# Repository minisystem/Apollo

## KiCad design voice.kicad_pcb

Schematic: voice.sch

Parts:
C1, C2: 0.01μ; SM0603-C-JRL
C3, C40, C41, C42, C43, C44, C45, C46, C47, C48, C49, C50, C51, C52, C53, C54, C55, C56, C57, C58, C59, C60, C61, C62, C63, C64, C65, C66, C67: 0.1μ; SM0603-C-JRL
C4: 10p; SM0603-C-JRL
C5, C12, C13: 0.47μ; jrl_c_elec_4x5.3
C6: 680p; SM0603-C-JRL
C7, C8, C9, C10: 270pF; SM0603-C-JRL
C11: 15p; SM0603-C-JRL
C14: 47pF; SM0603-C-JRL
D1, D2, D3, D4: 1N4148; SOD323-C1A2
J1: DDR3-DIMM; DDR3-DIMM-MO-269-mask-fix
Q1, Q2, Q3, Q4, Q10, Q11, Q14, Q15, Q17, Q18, Q20, Q39: 2SA1832; SOT416-SC75
Q5, Q6, Q7, Q8, Q9, Q12, Q13: 2SK208-GR; SOT23-132-JRL
Q16: 2SA1618; SOT-353_SC-70-5
Q19: 2SK208-GR; SC-59
Q21: 2SC4738; SOT416-SC75
R1, R4, R6, R74: 4.7meg; SM0603-R-JRL; Digikey P10.0KCCT-ND
R2: 47K; SM0603-R-JRL; Digikey P10.0KCCT-ND
R3, R5, R19, R49, R73, R76, R88, R89, R107, R252: 12K; SM0603-R-JRL; Digikey P10.0KCCT-ND
R7: 10K; SM0603-R-JRL; Digikey P10.0KCCT-ND
R8, R21: 12K; SM0603-R-JRL; Digikey P56.0KCCT-ND
R9, R105: 27K; SM0603-R-JRL; Digikey P56.0KCCT-ND
R10: 10K; SM0603-R-JRL; Digikey P56.0KCCT-ND
R11, R12, R13, R14: 330; SM0603-R-JRL; Digikey P10.0KCCT-ND
R15, R26, R43, R72, R91, R92, R95, R98, R103: 100K; SM0603-R-JRL; Digikey P10.0KCCT-ND
R16, R17, R28: 68K; SM0603-R-JRL; Digikey P56.0KCCT-ND
R18, R52: 33K; SM0603-R-JRL; Digikey P10.0KCCT-ND
R20: 15k; SM0603-R-JRL; Digikey P10.0KCCT-ND
R22, R30: 18K; SM0603-R-JRL; Digikey P10.0KCCT-ND
R23, R24: 510; SM0603-R-JRL; Digikey P10.0KCCT-ND
R25: 30K; SM0603-R-JRL; Digikey P10.0KCCT-ND
R27: 15K; SM0603-R-JRL; Digikey P10.0KCCT-ND
R29, R32, R114: 22K; SM0603-R-JRL; Digikey P56.0KCCT-ND
R31, R118: 22K; SM0603-R-JRL; Digikey P10.0KCCT-ND
R33, R48: 100K; SM0603-R-JRL
R34, R44: 150K; SM0603-R-JRL
R35: 10K; SM0603-R-JRL
R36, R109: 150K; SM0603-R-JRL; Digikey P10.0KCCT-ND
R37, R38, R39, R40: 18K; SM0603-R-JRL
R41: 22K; SM0603-R-JRL
R42, R53, R104: 1.5K; SM0603-R-JRL
R45, R46, R47, R65, R66, R67, R68: 68K; SM0603-R-JRL
R50, R51, R63, R64, R80, R81, R82, R83, R96, R97, R100, R101, R111, R112, R254, R255: 470; SM0603-R-JRL; Digikey P10.0KCCT-ND
R54, R55, R56, R57: 33K; SM0603-R-JRL
R58, R75, R79, R84, R253: 47K; SM0603-R-JRL; Digikey P56.0KCCT-ND
R59, R60, R61, R62: 560; SM0603-R-JRL
R69, R113: 1meg; SM0603-R-JRL; Digikey P10.0KCCT-ND
R70, R71, R86, R256: 18K; SM0603-R-JRL; Digikey P56.0KCCT-ND
R77: 2.2K; SM0603-R-JRL; Digikey P10.0KCCT-ND
R78, R85: 1meg; SM0603-R-JRL
R87: 470K; SM0603-R-JRL; Digikey P10.0KCCT-ND
R90, R94, R115, R117: 68K; SM0603-R-JRL; Digikey P10.0KCCT-ND
R93: 27K; SM0603-R-JRL; Digikey P10.0KCCT-ND
R99: 1K 3300 ppm/K; SM0805-HAND
R102: 56K; SM0603-R-JRL; Digikey P56.0KCCT-ND
R106: 1.5M; SM0603-R-JRL
R108: 43K; SM0603-R-JRL; Digikey P56.0KCCT-ND
R110: 180K; SM0603-R-JRL; Digikey P10.0KCCT-ND
R116: 82K; SM0603-R-JRL; Digikey P10.0KCCT-ND
TP1, TP2, TP3, TP4, TP5, TP6, TP7, TP8, TP9: TEST_POINT; TEST_POINT_SMALL
U1, U4: CD4053; TSSOP-16_4.4x5mm_Pitch0.65mm_jrl
U2, U5, U7, U8, U9, U10, U12, U14: LM13700; SO16-JRL
U3, U6, U13, U16: TA75S558F; SOT753_TSOP5_SC-74A
U11: TL072-; TSSOP8-JRL
U15: RC4558; TSSOP8-JRL

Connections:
+10V: R25.2; also elsewhere on the board
+12V: C40.1, C41.1, C42.1, C43.1, C44.1, C45.1, C46.1, C47.1, C48.1, C49.1, C50.1, C51.1, C52.1, C53.1, J1.2, J1.18, J1.36, J1.51, J1.61, J1.76, J1.87, J1.103, Q5.2 (S), Q6.2 (S), Q7.2 (S), Q8.2 (S), Q9.2 (S), R3.2, R5.2, R19.2, R31.2, R49.2, R69.2, R73.2, R76.2, R88.2, R89.2, R107.2, R252.2, U1.16 (Vdd), U2.11 (V+), U3.5 (V+), U4.16 (Vdd), U5.11 (V+), U6.5 (V+), U7.11 (V+), U8.11 (V+), U9.11 (V+), U10.11 (V+), U11.8 (V+), U12.11 (V+), U13.5 (V+), U14.11 (V+), U15.8 (V+), U16.5 (V+); also elsewhere on the board
-5V: U1.7 (Vee), U4.7 (Vee); also elsewhere on the board
-12V: C54.2, C55.2, C56.2, C57.2, C58.2, C59.2, C60.2, C61.2, C62.2, C63.2, C64.2, C65.2, C66.2, C67.2, J1.4, J1.20, J1.38, J1.53, J1.63, J1.78, J1.89, J1.105, R52.1, R54.1, R55.1, R56.1, R57.1, R106.2, U2.6 (V-), U3.2 (V-), U5.6 (V-), U6.2 (V-), U7.6 (V-), U8.6 (V-), U9.6 (V-), U10.6 (V-), U11.4 (V-), U12.6 (V-), U13.2 (V-), U14.6 (V-), U15.4 (V-), U16.2 (V-); also elsewhere on the board
AUX: J1.108, R253.1
AUX_LEVEL: J1.107, R256.1
CROSSMOD: J1.29, R16.1
ENV1_A: J1.94; also elsewhere on the board
ENV1_D: J1.95; also elsewhere on the board
ENV1_POL: J1.91; also elsewhere on the board
ENV1_R: J1.97; also elsewhere on the board
ENV1_S: J1.96; also elsewhere on the board
ENV2_A: J1.98; also elsewhere on the board
ENV2_D: J1.99; also elsewhere on the board
ENV2_R: J1.101; also elsewhere on the board
ENV2_S: J1.100; also elsewhere on the board
ENV_1: Q19.1 (D), R9.1, R20.2, R113.2; also elsewhere on the board
ENV_2: R102.2, R116.2; also elsewhere on the board
ENV_SEL: D3.1 (K), J1.72, R117.1
GATE: J1.92; also elsewhere on the board
HPF: J1.59, R71.1
Iabc: Q16.5 (C), R37.2, R38.2, R39.2, R40.2
KCV_1: J1.6, R95.1; also elsewhere on the board
KCV_2: J1.40; also elsewhere on the board
LEVEL: J1.83, R98.1
LFO: J1.55, R27.1
NOISE: J1.22; also elsewhere on the board
unnamed: C1.1, R1.1, R2.1, R15.2, U2.5, U3.3 (-)
unnamed: C1.2, R2.2, R7.1, R10.1, TP1.1, U3.4
unnamed: C2.1, R18.1, R26.2, U6.3 (-), U10.5
unnamed: C3.1, R34.1
unnamed: C3.2, Q5.1 (D), R36.2, R44.1, R52.2, TP2.1
unnamed: C4.1, C6.2, R43.2, TP3.1, U11.1
unnamed: C4.2, R43.1, U5.5, U5.12, U10.12, U11.2 (-)
unnamed: C5.1 (+), R48.2
unnamed: C5.2 (-), Q9.1 (D), Q12.1 (D), R57.2, R68.1, R78.2, TP5.1
unnamed: C6.1, Q5.3 (G), U7.5
unnamed: C7.1, Q6.3 (G), U8.5
unnamed: C8.1, Q7.3 (G), U8.12
unnamed: C9.1, Q8.3 (G), U9.5
unnamed: C10.1, Q9.3 (G), U9.12
unnamed: C11.1, R72.1, U12.5, U13.3 (-)
unnamed: C11.2, R72.2, R77.1, TP6.1, U13.4
unnamed: C12.1 (+), Q12.2 (S)
unnamed: C12.2 (-), R75.1
unnamed: C13.1 (+), Q13.2 (S)
unnamed: C13.2 (-), R84.1
unnamed: C14.1, R104.2, U16.4
unnamed: C14.2, Q16.4 (C), R106.1, U16.3 (-)
unnamed: D1.2 (A), Q12.3 (G), R78.1
unnamed: D2.2 (A), Q13.3 (G), R85.1
unnamed: D3.2 (A), Q19.3 (G), R113.1
unnamed: D4.1 (K), R117.2, R118.1
unnamed: Q1.2 (E), R16.2
unnamed: Q1.3 (C), U2.16
unnamed: Q2.2 (E), R17.2
unnamed: Q2.3 (C), U2.1
unnamed: Q3.2 (E), R28.2
unnamed: Q3.3 (C), U10.1
unnamed: Q4.2 (E), R41.2
unnamed: Q4.3 (C), U7.16
unnamed: Q6.1 (D), R45.2, R54.2, R65.1
unnamed: Q8.1 (D), R47.2, R56.2, R67.1
unnamed: Q10.2 (E), R70.2
unnamed: Q10.3 (C), U5.16
unnamed: Q11.2 (E), R69.1, R71.2
unnamed: Q11.3 (C), U7.1
unnamed: Q7.1 (D), Q13.1 (D), R46.2, R55.2, R66.1, R85.2, TP4.1
unnamed: Q14.2 (E), U12.12
unnamed: Q14.3 (C), U12.1
unnamed: Q15.2 (E), R86.2
unnamed: Q15.3 (C), U5.1
unnamed: Q16.1 (B), R93.2, R99.1, TP8.1
unnamed: Q16.2 (E), R104.1
unnamed: Q17.2 (E), R102.1
unnamed: Q17.3 (C), U12.16
unnamed: Q18.2 (E), R105.1
unnamed: Q18.3 (C), U14.16
unnamed: Q19.2 (S), R109.2
unnamed: Q20.2 (E), R114.1
unnamed: Q20.3 (C), U14.1
unnamed: Q21.1 (B), R118.2
unnamed: Q21.3 (C), R115.2, R116.1
unnamed: Q39.2 (E), R256.2
unnamed: Q39.3 (C), U10.16
unnamed: R3.1, U2.15
unnamed: R5.1, U2.2
unnamed: R7.2, U1.2 (Y0)
unnamed: R10.2, U1.12 (Y0)
unnamed: R8.2, R11.2, U2.14 (+)
unnamed: R4.1, R12.2, U2.13 (-)
unnamed: R9.2, R13.2, U2.3 (+)
unnamed: R6.1, R14.2, U2.4 (-)
unnamed: R19.1, U10.2
unnamed: R20.1, R22.2, U4.5 (Y0)
unnamed: R21.1, U4.15 (Z)
unnamed: R21.2, R23.2, U10.3 (+)
unnamed: R24.2, U10.4 (-)
unnamed: R25.1, R27.2, U4.3 (Y1)
unnamed: R29.2, U4.9 (S)
unnamed: R30.2, R31.1, U4.2 (Y0)
unnamed: R32.2, U4.10 (S)
unnamed: R33.1, R42.1, U7.14 (+)
unnamed: R33.2, R34.2, R35.2
unnamed: R36.1, R50.2, U7.4 (-)
unnamed: R37.1, U8.1
unnamed: R38.1, U8.16
unnamed: R39.1, U9.1
unnamed: R40.1, U9.16
unnamed: R44.2, R59.2, R65.2, U7.12, U8.4 (-)
unnamed: R45.1, R60.2, R66.2, U8.13 (-)
unnamed: R46.1, R61.2, R67.2, U9.4 (-)
unnamed: R47.1, R62.2, R68.2, U9.13 (-)
unnamed: R48.1, R53.2, U7.13 (-)
unnamed: R49.1, U5.15
unnamed: R51.2, U7.3 (+)
unnamed: R58.2, R63.2, U5.13 (-)
unnamed: R64.2, U5.14 (+)
unnamed: R73.1, U12.2
unnamed: R74.1, R81.2, U12.3 (+)
unnamed: R75.2, R80.2, R84.2, TP7.1, U12.4 (-)
unnamed: R76.1, U5.2
unnamed: R79.2, R82.2, U5.4 (-)
unnamed: R83.2, U5.3 (+)
unnamed: R88.1, U12.15
unnamed: R89.1, U14.15
unnamed: R90.2, R93.1, U15.7
unnamed: R91.1, R92.2, U15.2 (-)
unnamed: R91.2, R94.1, U15.1
unnamed: R96.2, U12.13 (-)
unnamed: R97.2, R98.2, U12.14 (+)
unnamed: R100.2, U14.13 (-)
unnamed: R94.2, R101.2, U14.14 (+)
unnamed: R95.2, R103.2, U15.3 (+)
unnamed: R107.1, U14.2
unnamed: R87.1, R90.1, R108.1, R110.2, U14.5, U14.12, U15.6 (-)
unnamed: R109.1, R111.2, R115.1, TP9.1, U14.3 (+)
unnamed: R112.2, U14.4 (-)
unnamed: R252.1, U10.15
unnamed: R253.2, R254.2, U10.13 (-)
unnamed: R255.2, U10.14 (+)
unnamed: U4.1 (Y1), U4.4 (Z)
unnamed: U11.6 (-), U11.7
OUT: J1.85, R77.2
PW/PWM: J1.26, R32.1
PWM: C2.2, R18.2, U6.4; also elsewhere on the board
PWM_LEVEL: J1.28, R28.1
PWM_SEL: J1.25, R29.1
RES_CTRL: J1.80, R41.1
SYNC_CTRL: J1.14; also elsewhere on the board
VCA_BAL: J1.82, R74.2
VCF_12dB: D2.1 (K), J1.73
VCF_24dB: D1.1 (K), J1.74
VCF_CUTOFF: J1.69, R108.2
VCF_ENV_MOD: J1.70, R114.2
VCF_KF: J1.67, R105.2
VCF_TUNE: J1.68, R87.2
VCO1: R58.1; also elsewhere on the board
VCO1_AUTOTUNE: J1.12; also elsewhere on the board
VCO1_INIT: J1.8; also elsewhere on the board
VCO1_LEVEL: J1.57, R70.1
VCO1_MOD: U1.15 (Z); also elsewhere on the board
VCO1_MOD_SUM: J1.9; also elsewhere on the board
VCO1_MOD_SW: J1.23, U1.10 (S)
VCO1_RANGE: J1.65, R92.1
VCO1_TRI_SYM: J1.10; also elsewhere on the board
VCO1_WF-0: J1.15; also elsewhere on the board
VCO1_WF-1: J1.16; also elsewhere on the board
VCO1_XMOD: U2.12; also elsewhere on the board
VCO2: R8.1, R79.1; also elsewhere on the board
VCO2_AUTOTUNE: J1.46; also elsewhere on the board
VCO2_INIT: J1.42; also elsewhere on the board
VCO2_LEVEL: J1.58, R86.1
VCO2_MOD: U1.14 (Z); also elsewhere on the board
VCO2_MOD_SUM: J1.43; also elsewhere on the board
VCO2_MOD_SW: J1.24, U1.11 (S)
VCO2_TRI_SYM: J1.44; also elsewhere on the board
VCO2_WF-0: J1.48; also elsewhere on the board
VCO2_WF-1: J1.49; also elsewhere on the board
VCO_ENV_MOD: J1.31, R17.1
VCO_ENV_MOD_BAL: J1.32, R6.2
VCO_LFO_MOD: J1.33, R15.1
VCO_MOD_BAL: J1.34, R1.2
XMOD_BAL: J1.30, R4.2

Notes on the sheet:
VCF Exponential converter
check polarity
SIMULATE VCA CONTROL
56K - 100K
18K-28K
SIMULATE VCF CONTROL need to change to low offset low Iabc configuration
22K - 32K
39K - 49K
VCF CONTROL
low offset LM13700: increase input level, reduce Iabc relative to BA662 configuration
(180K)
+10V reference in JP8
VCF CUTOFF is the sum of CUTOFF, LFO, VCF PEDAL and VCF MOD
(100K)
LFO modulation generated from one VCA on each module controller board (2 MCBs for 2 part timbrality)
VOICE MODULE
CROSS MODULATION
VCO PITCH MODULATION
VCF MODULATION
PULSE WIDTH MODULATION
VCA
HPF
VC MIXER
VCF
24 dB/oct
12 dB/oct
'LEVEL' is stepped LFO modulation offset and controlled by 'VCA LEVEL' CV - see MCB
CD4053s are separate ICs on JP8 module board. Because of cross talk?
Maybe JFET shunts here?
Simulated. Need to investigate further and test original JP8 VCA modulation behaviour. Not getting good offness when LEVEL CV is 0V.
J112 Vgs(off) isn't low enough to block -ve inverted envelope voltages with -11V gate. Lower ENV amplitude or find different FET? ON Semi TF412S has low Vgs{off) - will probably work 2SK932 and J201 also look promising
ENV_SEL needs to swing close +ve and -ve rail. To keep JFET off need <= -11V.
When LEVEL CV = 0V there is some bleedthrough of ENV_2 signal. When LEVEL CV < 0V then there is no output. Amount of bleedthrough varies from voice to voice of JP8
OFFSET
-11V to +12V
-11V to +12V switch
10V switch
MOD CONTROL CV
DIRECT CV
OUTPUT

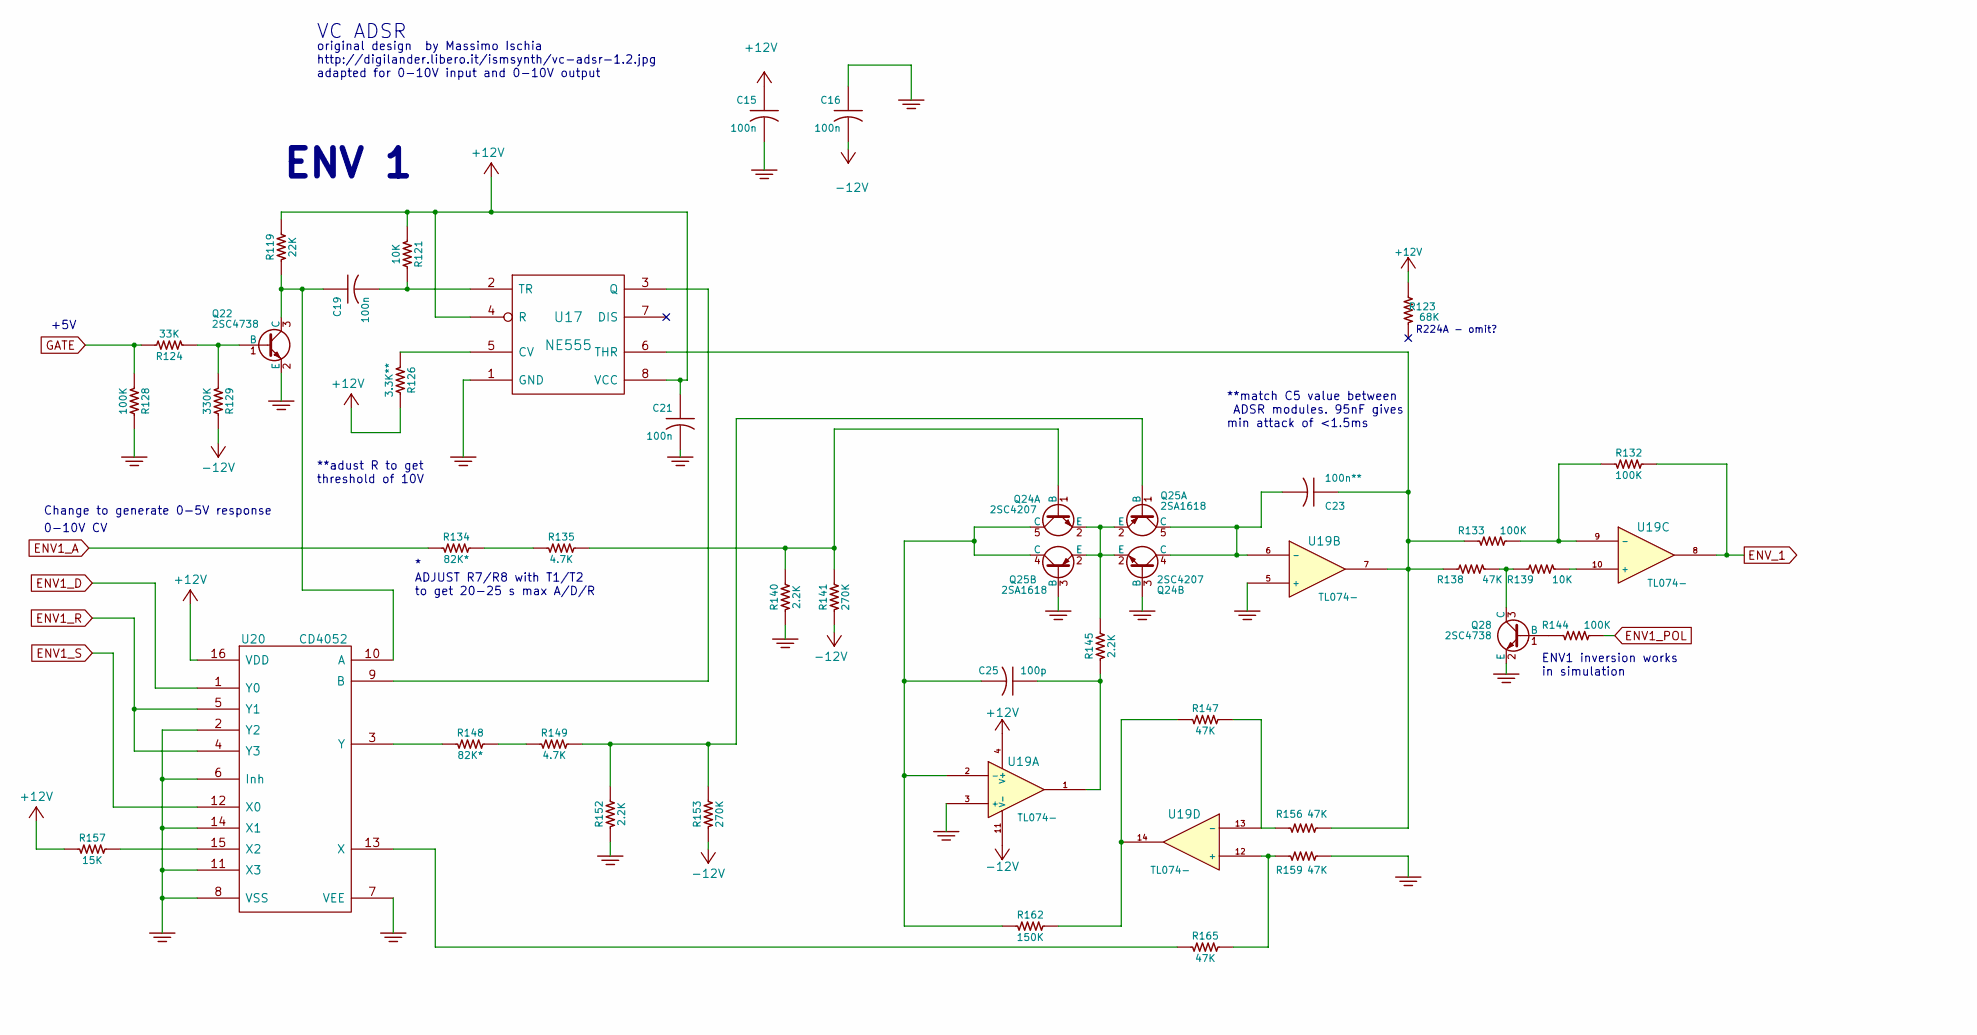
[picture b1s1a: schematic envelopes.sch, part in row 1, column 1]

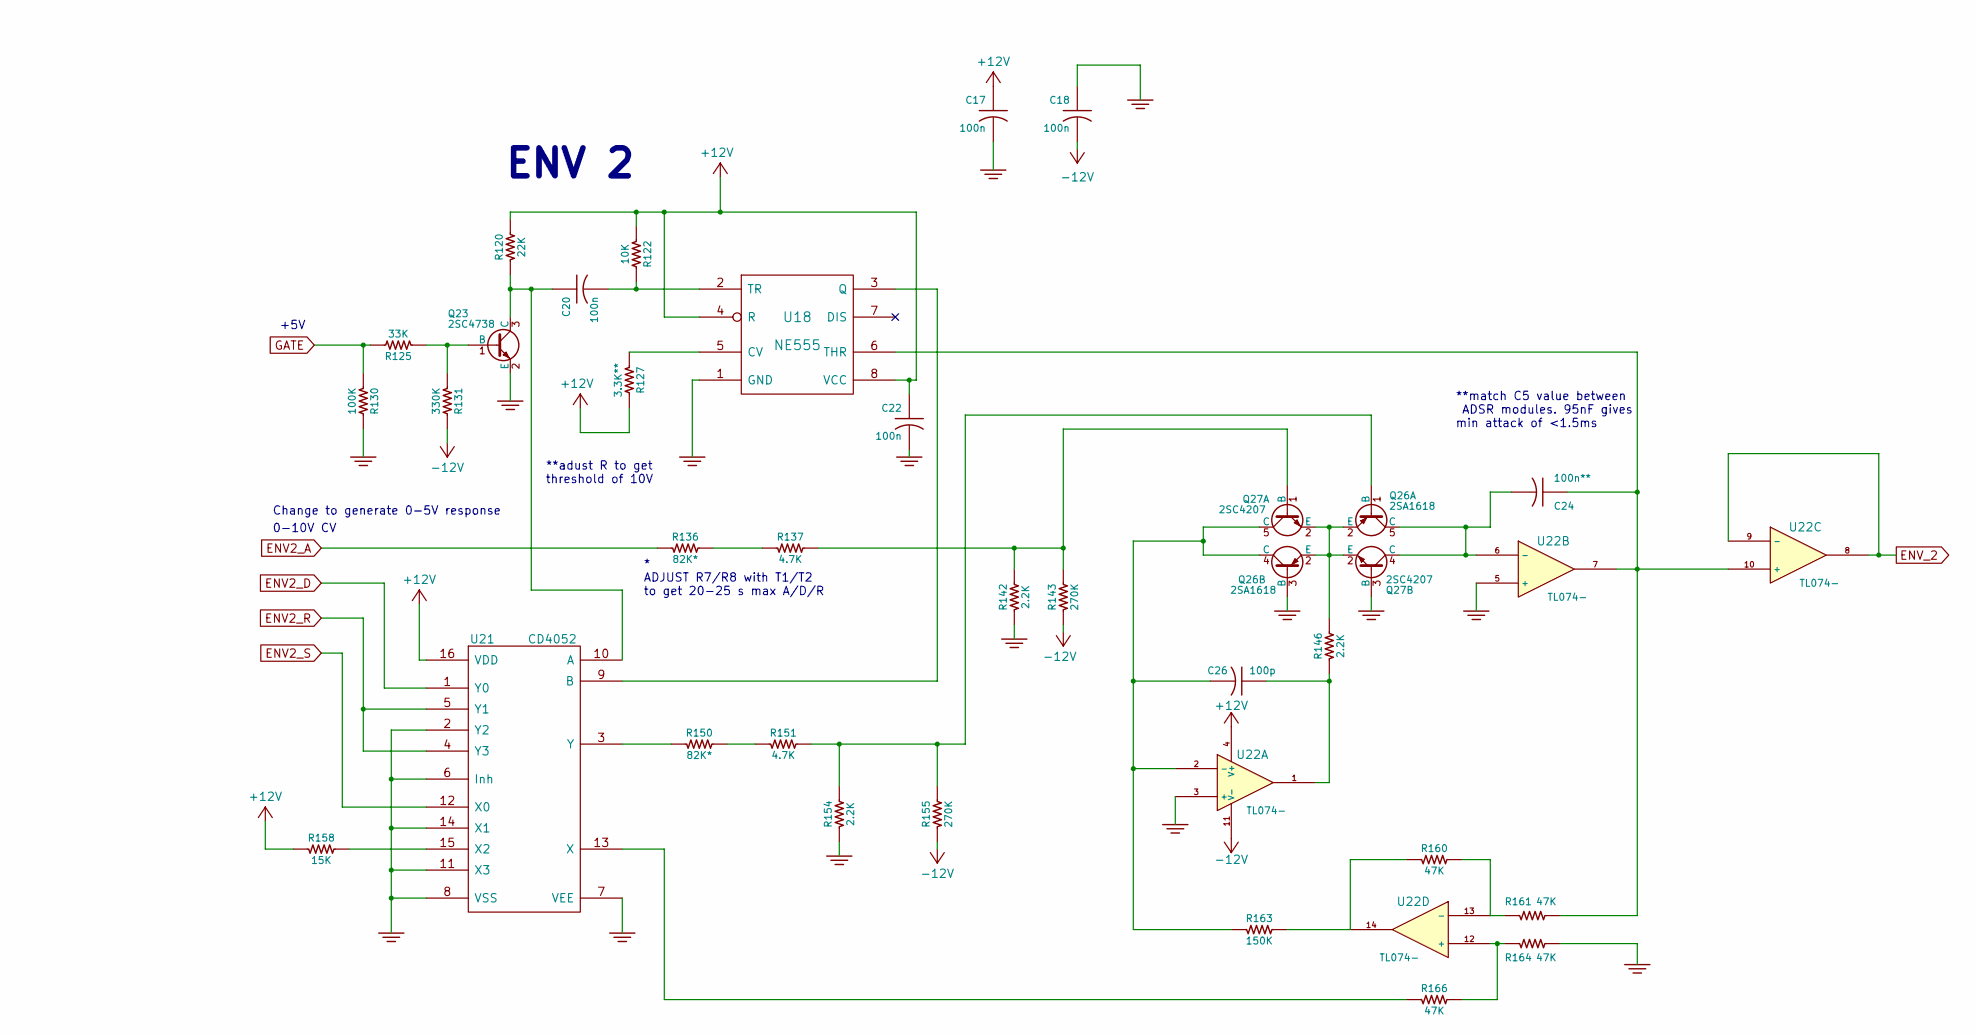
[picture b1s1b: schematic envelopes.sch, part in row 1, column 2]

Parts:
C15, C16, C17, C18, C19, C20, C21, C22: 100n; SM0603-C-JRL
C23, C24: 100n**; SM0603-C-JRL
C25, C26: 100p; SM0603-C-JRL
Q22, Q23, Q28: 2SC4738; SOT416-SC75
Q24, Q27: 2SC4207; SOT-353_SC-70-5
Q25, Q26: 2SA1618; SOT-353_SC-70-5
R119, R120: 22K; SM0603-R-JRL
R121, R122, R139: 10K; SM0603-R-JRL
R123: 68K; SM0603-R-JRL; Digikey P10.0KCCT-ND
R124, R125: 33K; SM0603-R-JRL
R126, R127: 3.3K**; SM0603-R-JRL
R128, R130, R132, R133, R144: 100K; SM0603-R-JRL
R129, R131: 330K; SM0603-R-JRL
R134, R136, R148, R150: 82K*; SM0603-R-JRL
R135, R137, R149, R151: 4.7K; SM0603-R-JRL
R138, R147, R156, R159, R160, R161, R164, R165, R166: 47K; SM0603-R-JRL
R140, R142, R145, R146, R152, R154: 2.2K; SM0603-R-JRL
R141, R143, R153, R155: 270K; SM0603-R-JRL
R157, R158: 15K; SM0603-R-JRL
R162, R163: 150K; SM0603-R-JRL
U17, U18: NE555; TSSOP8-JRL
U19, U22: TL074-; TSSOP-14_4.4x5mm_Pitch0.65mm
U20, U21: CD4052; TSSOP-16_4.4x5mm_Pitch0.65mm

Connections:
+12V: C15.1, C17.1, C21.1, C22.1, R119.2, R120.2, R121.1, R122.1, R123.2, R126.2, R127.2, R157.1, R158.1, U17.4 (R), U17.8 (VCC), U18.4 (R), U18.8 (VCC), U19.4 (V+), U20.16 (VDD), U21.16 (VDD), U22.4 (V+); also elsewhere on the board
-12V: C16.2, C18.2, R129.2, R131.2, R141.1, R143.1, R153.1, R155.1, U19.11 (V-), U22.11 (V-); also elsewhere on the board
ENV1_A: R134.1; also elsewhere on the board
ENV1_D: U20.1 (Y0); also elsewhere on the board
ENV1_POL: R144.2; also elsewhere on the board
ENV1_R: U20.4 (Y3), U20.5 (Y1); also elsewhere on the board
ENV1_S: U20.12 (X0); also elsewhere on the board
ENV2_A: R136.1; also elsewhere on the board
ENV2_D: U21.1 (Y0); also elsewhere on the board
ENV2_R: U21.4 (Y3), U21.5 (Y1); also elsewhere on the board
ENV2_S: U21.12 (X0); also elsewhere on the board
ENV_1: R132.2, U19.8; also elsewhere on the board
ENV_2: U22.8, U22.9 (-); also elsewhere on the board
GATE: R124.2, R125.2, R128.1, R130.1; also elsewhere on the board
unnamed: C19.1, Q22.3 (C), R119.1, U20.10 (A)
unnamed: C19.2, R121.2, U17.2 (TR)
unnamed: C20.1, Q23.3 (C), R120.1, U21.10 (A)
unnamed: C20.2, R122.2, U18.2 (TR)
unnamed: C23.1, R133.1, R138.1, R156.2, U17.6 (THR), U19.7
unnamed: C23.2, Q24.4 (C), Q25.5 (C), U19.6 (-)
unnamed: C24.1, R161.2, U18.6 (THR), U22.7, U22.10 (+)
unnamed: C24.2, Q26.5 (C), Q27.4 (C), U22.6 (-)
unnamed: C25.1, R145.1, U19.1
unnamed: C25.2, Q24.5 (C), Q25.4 (C), R162.1, U19.2 (-)
unnamed: C26.1, R146.1, U22.1
unnamed: C26.2, Q26.4 (C), Q27.5 (C), R163.1, U22.2 (-)
unnamed: Q22.1 (B), R124.1, R129.1
unnamed: Q23.1 (B), R125.1, R131.1
unnamed: Q24.1 (B), R135.2, R140.2, R141.2
unnamed: Q24.2 (E), Q25.2 (E), R145.2
unnamed: Q25.1 (B), R149.2, R152.2, R153.2
unnamed: Q26.1 (B), R151.2, R154.2, R155.2
unnamed: Q26.2 (E), Q27.2 (E), R146.2
unnamed: Q27.1 (B), R137.2, R142.2, R143.2
unnamed: Q28.1 (B), R144.1
unnamed: Q28.3 (C), R138.2, R139.1
unnamed: R126.1, U17.5 (CV)
unnamed: R127.1, U18.5 (CV)
unnamed: R132.1, R133.2, U19.9 (-)
unnamed: R134.2, R135.1
unnamed: R136.2, R137.1
unnamed: R139.2, U19.10 (+)
unnamed: R147.1, R162.2, U19.14
unnamed: R147.2, R156.1, U19.13 (-)
unnamed: R148.1, U20.3 (Y)
unnamed: R148.2, R149.1
unnamed: R150.1, U21.3 (Y)
unnamed: R150.2, R151.1
unnamed: R157.2, U20.15 (X2)
unnamed: R158.2, U21.15 (X2)
unnamed: R159.1, R165.2, U19.12 (+)
unnamed: R160.1, R163.2, U22.14
unnamed: R160.2, R161.1, U22.13 (-)
unnamed: R164.1, R166.2, U22.12 (+)
unnamed: R165.1, U20.13 (X)
unnamed: R166.1, U21.13 (X)
unnamed: U17.3 (Q), U20.9 (B)
unnamed: U18.3 (Q), U21.9 (B)

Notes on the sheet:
**adust R to get threshold of 10V
* ADJUST R7/R8 with T1/T2 to get 20-25 s max A/D/R
**match C5 value between ADSR modules. 95nF gives min attack of <1.5ms
0-10V CV
+5V
VC ADSR
original design by Massimo Ischia http://digilander.libero.it/ismsynth/vc-adsr-1.2.jpg adapted for 0-10V input and 0-10V output
ENV1 inversion works in simulation
R224A - omit?
ENV 1
ENV 2
Change to generate 0-5V response

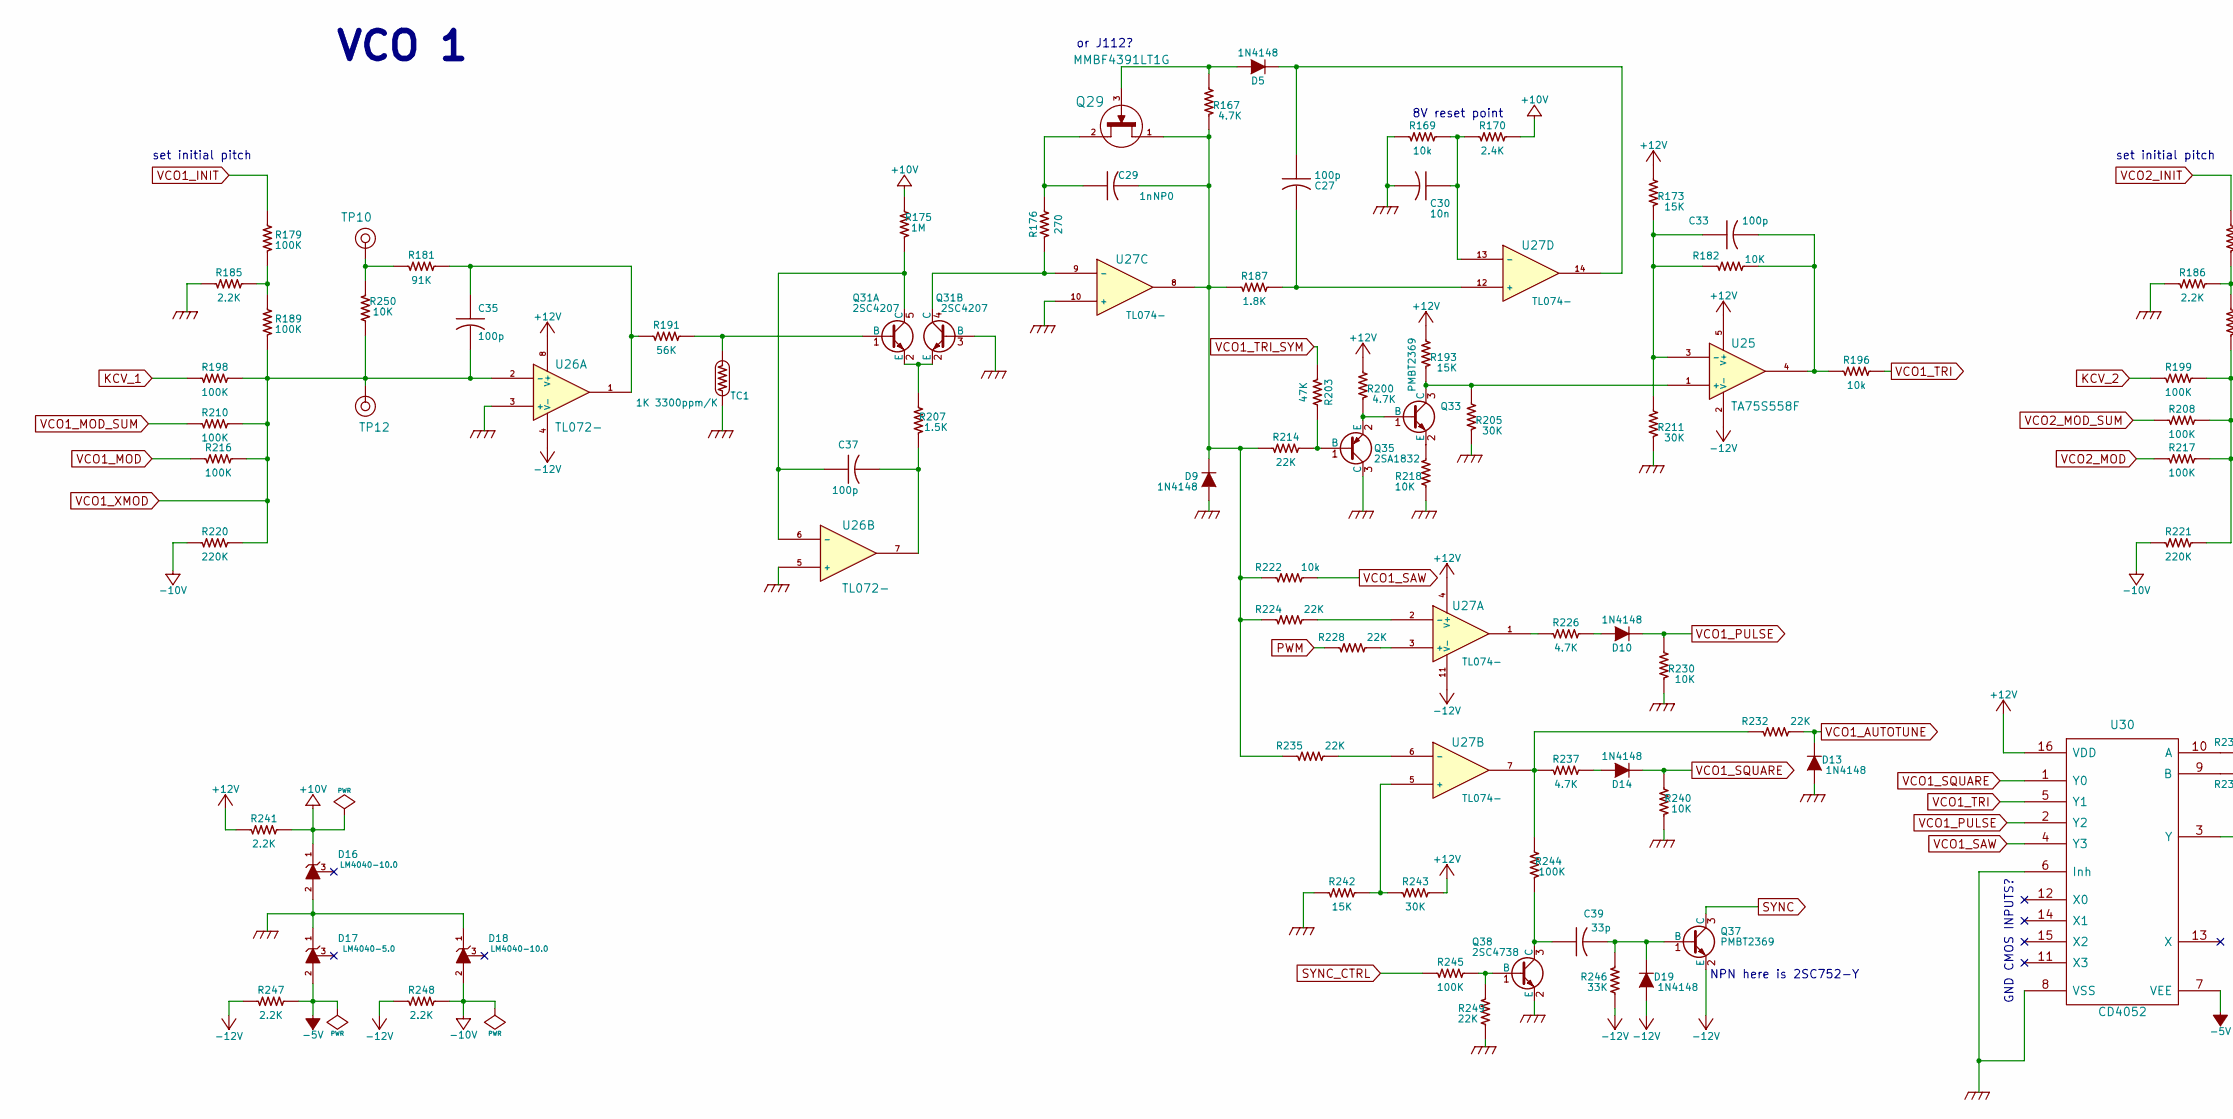
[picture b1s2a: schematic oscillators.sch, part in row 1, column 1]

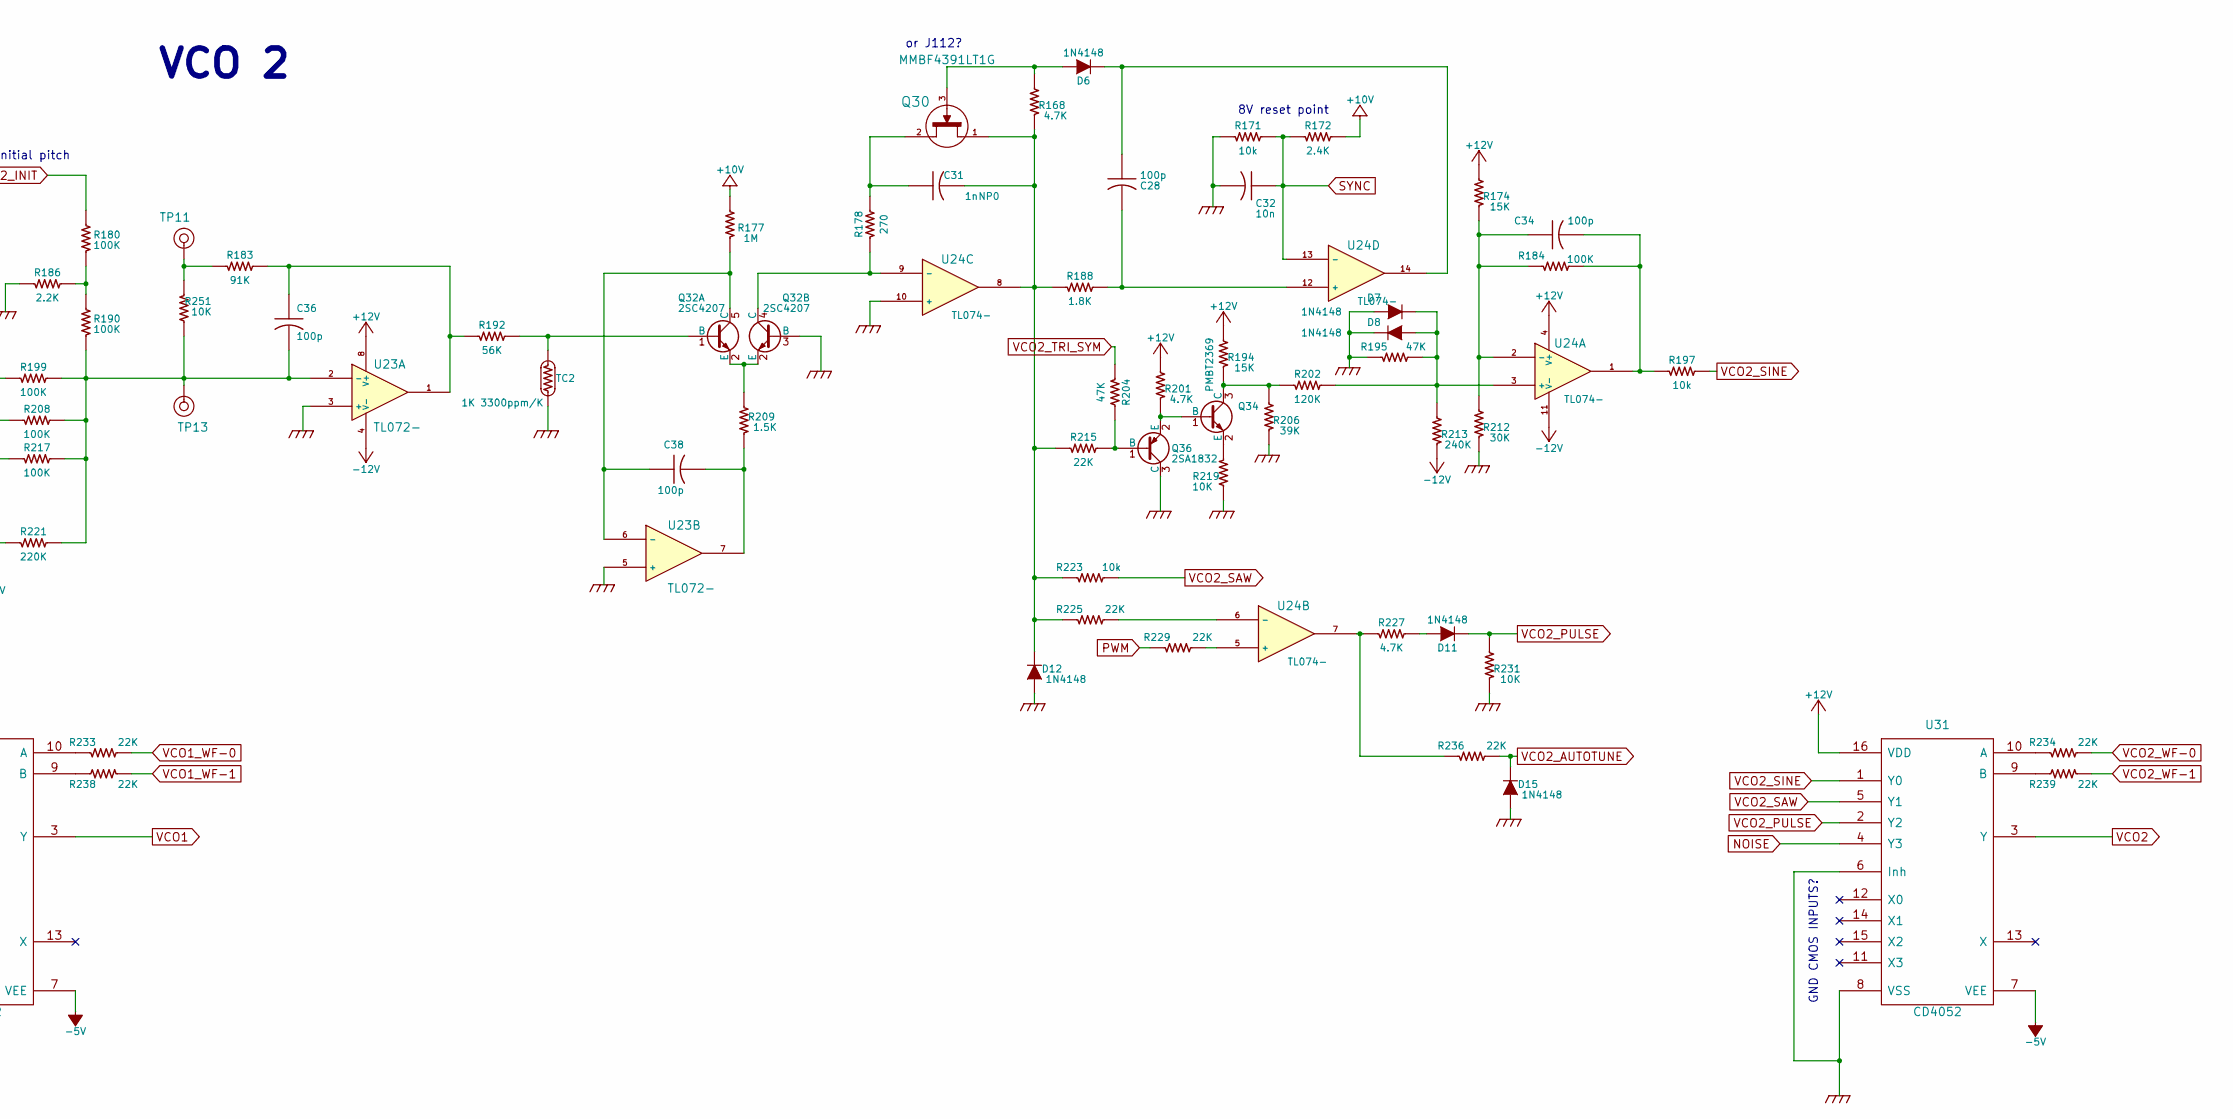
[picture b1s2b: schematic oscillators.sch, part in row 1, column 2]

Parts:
C27, C28, C33, C34: 100p; SM0603-C-JRL
C29, C31: 1n; SM0805-HAND-C
C30, C32: 10n; SM0603-C-JRL
C35, C36, C37, C38: 100p; SM0603-C-JRL; Digikey 399-1122-1-ND
C39: 33p; SM0603-C-JRL
D5, D6, D7, D8, D9, D10, D11, D12, D13, D14, D15, D19: 1N4148; SOD323-C1A2
D16, D18: LM4040-10.0; SOT23-132-JRL
D17: LM4040-5.0; SOT23-132-JRL
Q29, Q30: MMBF4391LT1G; SOT23-132-JRL
Q31, Q32: 2SC4207; SOT753_TSOP5_SC-74A
Q33, Q34, Q37: PMBT2369; SOT23-132-JRL
Q35, Q36: 2SA1832; SOT416-SC75
Q38: 2SC4738; SOT416-SC75
R167, R168, R200, R201, R226, R227, R237: 4.7K; SM0603-R-JRL; Digikey P10.0KCCT-ND
R169, R171, R196, R197, R222, R223: 10k; SM0603-R-JRL; Digikey P10.0KCCT-ND
R170, R172: 2.4K; SM0603-R-JRL; Digikey P10.0KCCT-ND
R173, R174, R193, R194, R242: 15K; SM0603-R-JRL; Digikey P10.0KCCT-ND
R175, R177: 1M; SM0603-R-JRL; Digikey P1.50MCCT-ND
R176, R178: 270; SM0603-R-JRL; Digikey P10.0KCCT-ND
R179, R180, R184, R189, R190, R244, R245: 100K; SM0603-R-JRL; Digikey P10.0KCCT-ND
R181, R183: 91K; SM0603-R-JRL; Digikey P91.0KCCT-ND
R182, R218, R219, R230, R231, R240: 10K; SM0603-R-JRL; Digikey P10.0KCCT-ND
R185, R186: 2.2K; SM0603-R-JRL; Digikey P91.0KCCT-ND
R187, R188: 1.8K; SM0603-R-JRL; Digikey P10.0KCCT-ND
R191, R192: 56K; SM0603-R-JRL; Digikey P56.0KCCT-ND
R195, R203, R204: 47K; SM0603-R-JRL; Digikey P10.0KCCT-ND
R198, R199, R208, R210, R216, R217: 100K; SM0603-R-JRL; Digikey P91.0KCCT-ND
R202: 120K; SM0603-R-JRL; Digikey P10.0KCCT-ND
R205, R211, R212, R243: 30K; SM0603-R-JRL; Digikey P10.0KCCT-ND
R206: 39K; SM0603-R-JRL; Digikey P10.0KCCT-ND
R207, R209: 1.5K; SM0603-R-JRL; Digikey P10.0KCCT-ND
R213: 240K; SM0603-R-JRL; Digikey P10.0KCCT-ND
R214, R215, R224, R225, R228, R229, R232, R233, R234, R235, R236, R238, R239, R249: 22K; SM0603-R-JRL; Digikey P10.0KCCT-ND
R220, R221: 220K; SM0603-R-JRL; Digikey P91.0KCCT-ND
R241, R247, R248: 2.2K; SM0603-R-JRL; Digikey P10.0KCCT-ND
R246: 33K; SM0603-R-JRL; Digikey P10.0KCCT-ND
R250, R251: 10K; SM0603-R-JRL; Digikey P56.0KCCT-ND
TC1, TC2: 1K 3300ppm/K; SM0805-HAND
TP10, TP11, TP12, TP13: TEST_POINT; TEST_POINT_SMALL
U23, U26: TL072-; TSSOP8-JRL
U24, U27: TL074-; TSSOP-14_4.4x5mm_Pitch0.65mm
U25: TA75S558F; SOT753_TSOP5_SC-74A
U30, U31: CD4052; TSSOP-16_4.4x5mm_Pitch0.65mm_jrl

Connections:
+10V: D16.1 (K), R170.2, R172.2, R175.2, R177.2, R241.2; also elsewhere on the board
+12V: R173.2, R174.2, R193.2, R194.2, R200.2, R201.2, R241.1, R243.2, U23.8 (V+), U24.4 (V+), U25.5 (V+), U26.8 (V+), U27.4 (V+), U30.16 (VDD), U31.16 (VDD); also elsewhere on the board
-5V: D17.2 (A), R247.2, U30.7 (VEE), U31.7 (VEE); also elsewhere on the board
-10V: D18.2 (A), R220.1, R221.1, R248.2
-12V: D19.2 (A), Q37.2 (E), R213.1, R246.1, R247.1, R248.1, U23.4 (V-), U24.11 (V-), U25.2 (V-), U26.4 (V-), U27.11 (V-); also elsewhere on the board
KCV_1: R198.1; also elsewhere on the board
KCV_2: R199.1; also elsewhere on the board
NOISE: U31.4 (Y3); also elsewhere on the board
unnamed: C27.1, D5.1 (K), U27.14
unnamed: C27.2, R187.2, U27.12 (+)
unnamed: C28.1, D6.1 (K), U24.14
unnamed: C28.2, R188.2, U24.12 (+)
unnamed: C29.1, Q29.2 (S), R176.2
unnamed: C29.2, D9.1 (K), Q29.1 (D), R167.1, R187.1, R214.1, R222.1, R224.1, R235.1, U27.8
unnamed: C30.1, R169.2, R170.1, U27.13 (-)
unnamed: C31.1, Q30.2 (S), R178.2
unnamed: C31.2, D12.1 (K), Q30.1 (D), R168.1, R188.1, R215.1, R223.1, R225.1, U24.8
unnamed: C33.1, R173.1, R182.1, R211.2, U25.3 (-)
unnamed: C33.2, R182.2, R196.1, U25.4
unnamed: C34.1, R174.1, R184.1, R212.2, U24.2 (-)
unnamed: C34.2, R184.2, R197.1, U24.1
unnamed: C35.1, R181.2, R191.1, U26.1
unnamed: C36.1, R183.2, R192.1, U23.1
unnamed: C36.2, R190.1, R199.2, R208.2, R217.2, R221.2, R251.2, TP13.1, U23.2 (-)
unnamed: C37.1, Q31.5 (C), R175.1, U26.6 (-)
unnamed: C37.2, R207.1, U26.7
unnamed: C38.1, Q32.5 (C), R177.1, U23.6 (-)
unnamed: C38.2, R209.1, U23.7
unnamed: C39.1, Q38.3 (C), R244.1
unnamed: C39.2, D19.1 (K), Q37.1 (B), R246.2
unnamed: D5.2 (A), Q29.3 (G), R167.2
unnamed: D6.2 (A), Q30.3 (G), R168.2
unnamed: D7.1 (K), D8.2 (A), R195.2, R202.2, R213.2, U24.3 (+)
unnamed: D10.2 (A), R226.2
unnamed: D11.2 (A), R227.2
unnamed: D14.2 (A), R237.2
unnamed: Q31.1 (B), R191.2, TC1.1
unnamed: Q31.2 (E), R207.2
unnamed: Q31.4 (C), R176.1, U27.9 (-)
unnamed: Q32.1 (B), R192.2, TC2.1
unnamed: Q32.2 (E), R209.2
unnamed: Q32.4 (C), R178.1, U24.9 (-)
unnamed: Q33.1 (B), Q35.2 (E), R200.1
unnamed: Q33.2 (E), R218.2
unnamed: Q33.3 (C), R193.1, R205.2, U25.1 (+)
unnamed: Q34.1 (B), Q36.2 (E), R201.1
unnamed: Q34.2 (E), R219.2
unnamed: Q34.3 (C), R194.1, R202.1, R206.2
unnamed: Q35.1 (B), R203.1, R214.2
unnamed: Q36.1 (B), R204.1, R215.2
unnamed: Q38.1 (B), R245.2, R249.2
unnamed: R179.1, R185.2, R189.2
unnamed: R180.1, R186.2, R190.2
unnamed: R181.1, R250.1, TP10.1
unnamed: R183.1, R251.1, TP11.1
unnamed: R224.2, U27.2 (-)
unnamed: R225.2, U24.6 (-)
unnamed: R226.1, U27.1
unnamed: R227.1, R236.1, U24.7
unnamed: R228.2, U27.3 (+)
unnamed: R229.2, U24.5 (+)
unnamed: R232.1, R237.1, R244.2, U27.7
unnamed: R233.1, U30.10 (A)
unnamed: R234.1, U31.10 (A)
unnamed: R235.2, U27.6 (-)
unnamed: R238.1, U30.9 (B)
unnamed: R239.1, U31.9 (B)
unnamed: R242.2, R243.1, U27.5 (+)
PWM: R228.1, R229.1; also elsewhere on the board
SYNC: C32.1, Q37.3 (C), R171.2, R172.1, U24.13 (-)
SYNC_CTRL: R245.1; also elsewhere on the board
VCO1: U30.3 (Y); also elsewhere on the board
VCO1_AUTOTUNE: D13.1 (K), R232.2; also elsewhere on the board
VCO1_INIT: R179.2; also elsewhere on the board
VCO1_MOD: R216.1; also elsewhere on the board
VCO1_MOD_SUM: R210.1; also elsewhere on the board
VCO1_PULSE: D10.1 (K), R230.2, U30.2 (Y2)
VCO1_SAW: R222.2, U30.4 (Y3)
VCO1_SQUARE: D14.1 (K), R240.2, U30.1 (Y0)
VCO1_TRI: R196.2, U30.5 (Y1)
VCO1_TRI_SYM: R203.2; also elsewhere on the board
VCO1_WF-0: R233.2; also elsewhere on the board
VCO1_WF-1: R238.2; also elsewhere on the board
VCO1_XMOD: C35.2, R189.1, R198.2, R210.2, R216.2, R220.2, R250.2, TP12.1, U26.2 (-); also elsewhere on the board
VCO2: U31.3 (Y); also elsewhere on the board
VCO2_AUTOTUNE: D15.1 (K), R236.2; also elsewhere on the board
VCO2_INIT: R180.2; also elsewhere on the board
VCO2_MOD: R217.1; also elsewhere on the board
VCO2_MOD_SUM: R208.1; also elsewhere on the board
VCO2_PULSE: D11.1 (K), R231.2, U31.2 (Y2)
VCO2_SAW: R223.2, U31.5 (Y1)
VCO2_SINE: R197.2, U31.1 (Y0)
VCO2_TRI_SYM: R204.2; also elsewhere on the board
VCO2_WF-0: R234.2; also elsewhere on the board
VCO2_WF-1: R239.2; also elsewhere on the board

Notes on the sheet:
or J112?
set initial pitch
VCO 1
VCO 2
NPN here is 2SC752-Y
8V reset point
GND CMOS INPUTS?

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
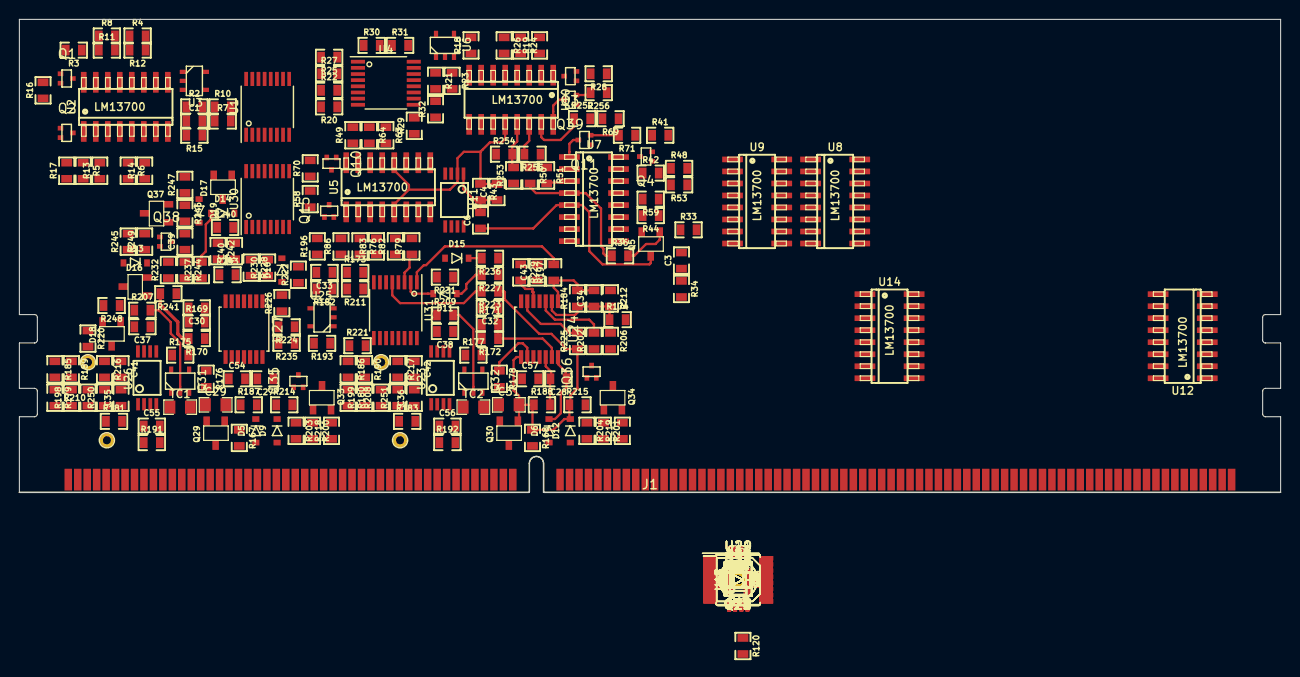
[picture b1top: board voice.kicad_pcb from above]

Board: 2 copper layers, 133.3 x 50.0 mm, 426 parts (0 on the bottom side), 298 nets.
